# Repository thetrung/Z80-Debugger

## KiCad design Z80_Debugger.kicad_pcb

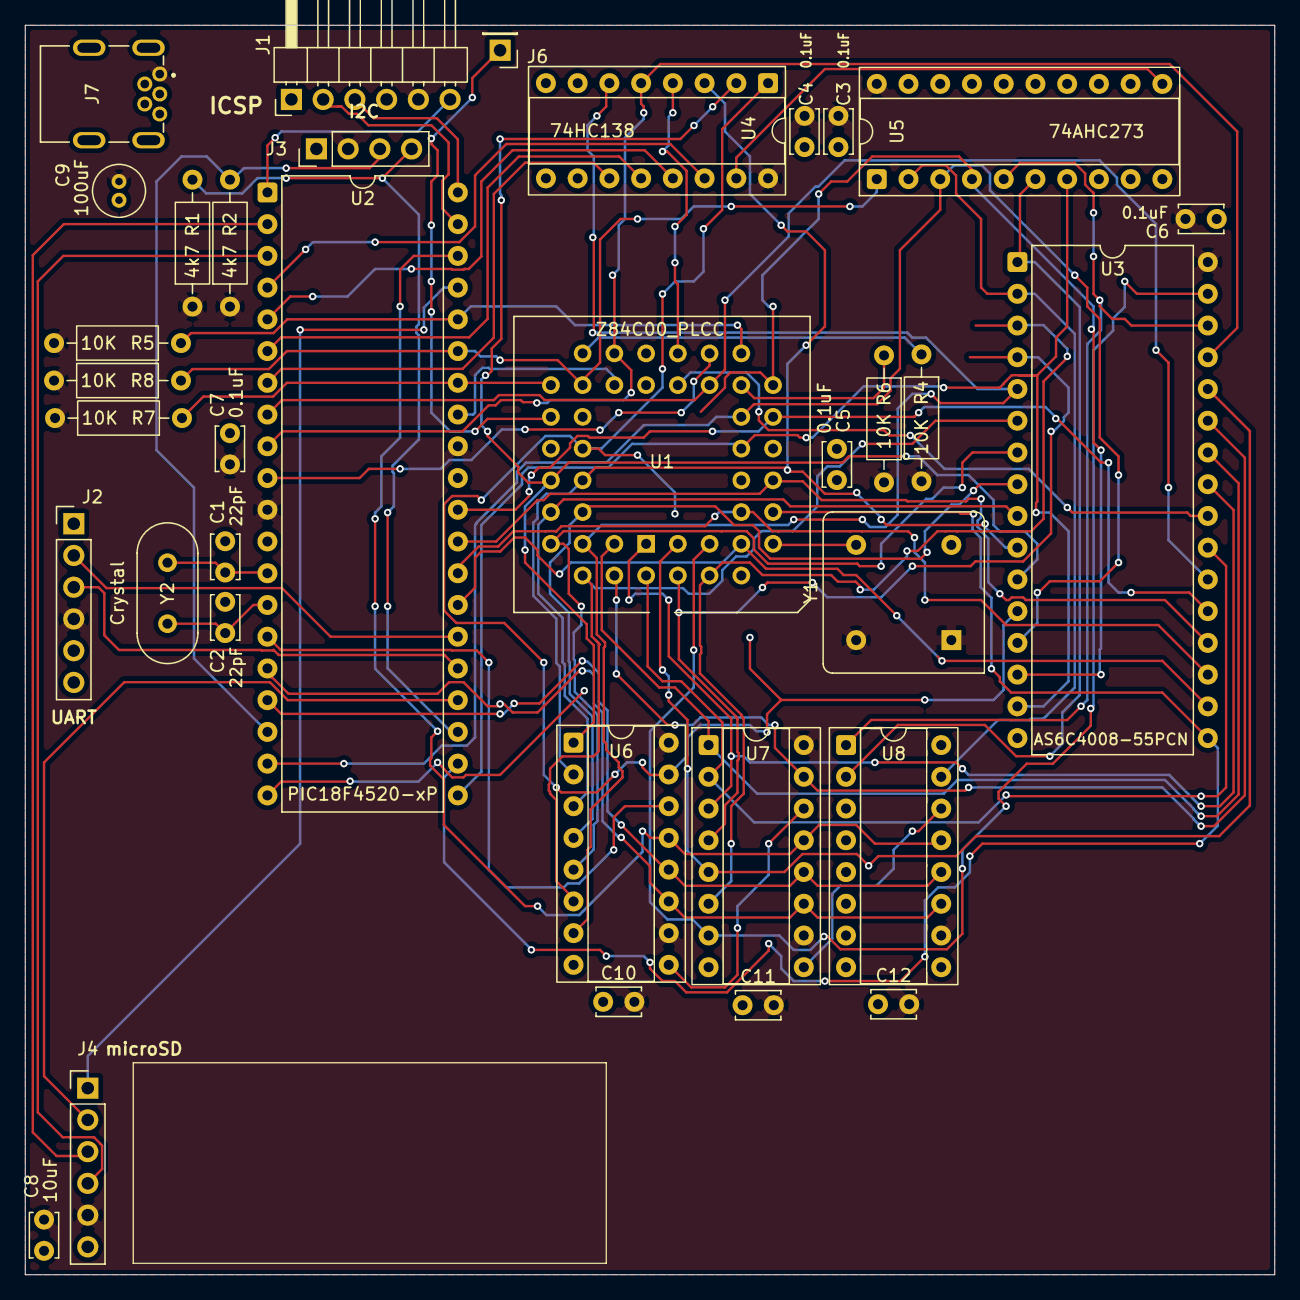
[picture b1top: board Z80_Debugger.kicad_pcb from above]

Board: 2 copper layers, 100.0 x 100.0 mm, 35 parts (0 on the bottom side), 66 nets.

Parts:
C1, C2: 22pF; C_Disc_D3.4mm_W2.1mm_P2.50mm
C3, C4, C5, C6, C7, C10, C11, C12: 0.1uF; C_Disc_D3.4mm_W2.1mm_P2.50mm
C8: 10uF; C_Disc_D3.4mm_W2.1mm_P2.50mm
C9: 100uF; C_Radial_D4.0mm_H5.0mm_P1.50mm
J1: ICSP; PinHeader_1x06_P2.54mm_Horizontal
J2: UART; PinHeader_1x06_P2.54mm_Vertical
J3: I2C; PinHeader_1x04_P2.54mm_Vertical
J4: microSD; PinHeader_1x06_P2.54mm_Vertical
J6: M1_O; PinHeader_1x01_P2.54mm_Vertical
J7: USB_B_Mini; USB_MINI_B_90_Angled
R1, R2: 4k7; R_Axial_DIN0207_L6.3mm_D2.5mm_P10.16mm_Horizontal
R4, R5, R6, R7, R8: 10K; R_Axial_DIN0207_L6.3mm_D2.5mm_P10.16mm_Horizontal
U1: Z84C00_PLCC; PLCC-44_THT-Socket
U2: PIC18F4520-xP; DIP-40_W15.24mm
U3: AS6C4008-55PCN; DIP-32_W15.24mm
U4: 74HC138; DIP-16_W7.62mm_Socket
U5: 74AHC273; DIP-20_W7.62mm_Socket
U6, U7, U8: 74HC595; DIP-16_W7.62mm_Socket
Y1: CXO_DIP8; Oscillator_DIP-8
Y2: Crystal; Crystal_HC49-4H_Vertical

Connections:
/0x80: U4.15 (~Y0), U5.11 (Cp)
/0x81: U2.4 (RA2), U4.14 (~Y1)
/0x82: U2.5 (RA3), U4.13 (~Y2)
/0x83: U2.6 (RA4), U4.12 (~Y3)
/0x84: U2.7 (RA5), U4.11 (~Y4)
/595E: U2.38 (RB5), U6.13 (~OE), U7.13 (~OE), U8.13 (~OE)
/A0: U1.34 (A_{0}), U3.12 (A0), U4.1 (A0), U6.15 (QA)
/A1: U1.35 (A_{1}), U3.11 (A1), U4.2 (A1), U6.1 (QB)
/A2: U1.36 (A_{2}), U3.10 (A2), U4.3 (A2), U6.2 (QC)
/A3: U1.37 (A_{3}), U3.9 (A3), U6.3 (QD)
/A4: U1.38 (A_{4}), U3.8 (A4), U6.4 (QE)
/A5: U1.39 (A_{5}), U3.7 (A5), U6.5 (QF)
/A6: U1.40 (A_{6}), U3.6 (A6), U6.6 (QG)
/A7: U1.41 (A_{7}), U3.5 (A7), U4.6 (E2), U6.7 (QH)
/A8: U1.42 (A_{8}), U3.27 (A8), U7.15 (QA)
/A9: U1.43 (A_{9}), U3.26 (A9), U7.1 (QB)
/A10: U1.44 (A_{10}), U3.23 (A10), U7.2 (QC)
/A11: U1.1 (A_{11}), U3.25 (A11), U7.3 (QD)
/A12: U1.2 (A_{12}), U3.4 (A12), U7.4 (QE)
/A13: U1.3 (A_{13}), U3.28 (A13), U7.5 (QF)
/A14: U1.4 (A_{14}), U3.3 (A14), U7.6 (QG)
/A15: U1.5 (A_{15}), U3.31 (A15), U7.7 (QH)
/A16: U3.2 (A16), U5.2 (Q0), U8.15 (QA)
/A17: U3.30 (A17), U5.5 (Q1), U8.1 (QB)
/A18: U3.1 (A18), U5.6 (Q2), U8.2 (QC)
/BUSACK: U1.27 (~BUSACK), U2.33 (RB0)
/BUSREQ: R7.1, U1.29 (~BUSREQ), U2.34 (RB1)
/CS: J4.1, U2.37 (RB4)
/D0: U1.16 (D_{0}), U2.19 (RD0), U3.13 (DQ0), U5.3 (D0)
/D1: U1.17 (D_{1}), U2.20 (RD1), U3.14 (DQ1), U5.4 (D1)
/D2: U1.14 (D_{2}), U2.21 (RD2), U3.15 (DQ2), U5.7 (D2)
/D3: U1.9 (D_{3}), U2.22 (RD3), U3.17 (DQ3)
/D4: U1.8 (D_{4}), U2.27 (RD4), U3.18 (DQ4)
/D5: U1.10 (D_{5}), U2.28 (RD5), U3.19 (DQ5)
/D6: U1.11 (D_{6}), U2.29 (RD6), U3.20 (DQ6)
/D7: U1.15 (D_{7}), U2.30 (RD7), U3.21 (DQ7)
/HALT: U1.20 (~HALT), U2.10 (RE2)
/INT: R5.1, U1.18 (~INT), U2.36 (RB3)
/IORQ: U1.22 (~IORQ), U4.4 (~E0)
/M1: J6.1 (Pin_1_1), U1.31 (~M1)
/MCLR: J1.6, U2.1 (RE3/~MCLR)
/MISO: J4.4, U2.3 (RA1)
/MOSI: J4.3, U2.2 (RA0)
/MREQ: U1.21 (~MREQ), U2.8 (RE0), U3.22 (CE#)
/NMI: R6.1, U1.19 (~NMI)
/OSC1: C1.1, U2.13 (RA7), Y2.2
/OSC2: C2.1, U2.14 (RA6), Y2.1
/PGC: J1.2, U2.39 (RB6)
/PGD: J1.3, U2.40 (RB7)
/RCLK: U2.17 (RC2), U6.12 (RCLK), U7.12 (RCLK), U8.12 (RCLK)
/RD: U1.23 (~RD), U3.24 (OE#)
/RESET: R8.1, U1.30 (~RESET), U2.35 (RB2), U5.1 (~Mr)
/RX: J2.2, U2.26 (RC7)
/SCK: J4.2, U2.24 (RC5)
/SCL: J3.3, R2.2, U2.18 (RC3)
/SDA: J3.4, R1.2, U2.23 (RC4)
/SER: U2.15 (RC0), U6.14 (SER)
/SRCLK: U2.16 (RC1), U6.11 (SRCLK), U7.11 (SRCLK), U8.11 (SRCLK)
/TX: J2.3, U2.25 (RC6)
/WAIT: R4.1, U1.28 (~WAIT)
/WR: U1.26 (~WR), U2.9 (RE1), U3.29 (WE#), U4.5 (~E1)
/Z80_CLK: U1.7 (~CLK), Y1.5 (OUT)
GND: C1.2, C2.2, C3.1, C4.1, C5.1, C6.1, C7.1, C8.1, C9.1, C10.1, C11.1, C12.1, J1.4, J2.6, J3.1, J4.6, J7.5 (GND), J7.6 (Shield), U1.33 (GND), U2.12 (VSS), U2.31 (VSS), U3.16 (VSS), U4.8 (GND), U5.8 (D3), U5.10 (GND), U5.13 (D4), U5.14 (D5), U5.17 (D6), U5.18 (D7), U6.8 (GND), U7.8 (GND), U8.8 (GND), Y1.4 (GND)
unnamed: U6.9 (QH'), U7.14 (SER)
unnamed: U7.9 (QH'), U8.14 (SER)
VCC: C3.2, C4.2, C5.2, C6.2, C7.2, C8.2, C9.2, C10.2, C11.2, C12.2, J1.5, J2.4, J3.2, J4.5, J7.1 (VBUS), R1.1, R2.1, R4.2, R5.2, R6.2, R7.2, R8.2, U1.13 (V_{CC}), U2.11 (VDD), U2.32 (VDD), U3.32 (VCC), U4.16 (VCC), U5.20 (VCC), U6.10 (~SRCLR), U6.16 (VCC), U7.10 (~SRCLR), U7.16 (VCC), U8.10 (~SRCLR), U8.16 (VCC), Y1.1 (EN), Y1.8 (Vcc)
